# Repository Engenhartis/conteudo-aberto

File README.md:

# conteudo-aberto
Conteúdo aberto disponibilizado pela Engenhartis.

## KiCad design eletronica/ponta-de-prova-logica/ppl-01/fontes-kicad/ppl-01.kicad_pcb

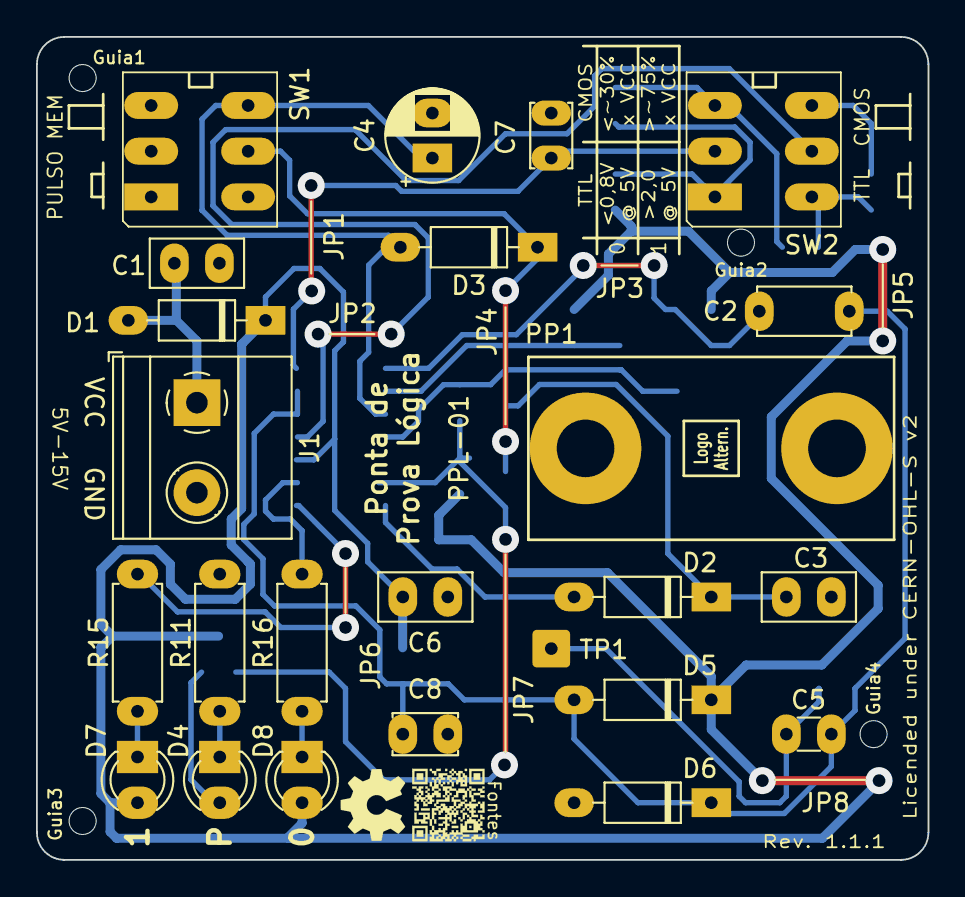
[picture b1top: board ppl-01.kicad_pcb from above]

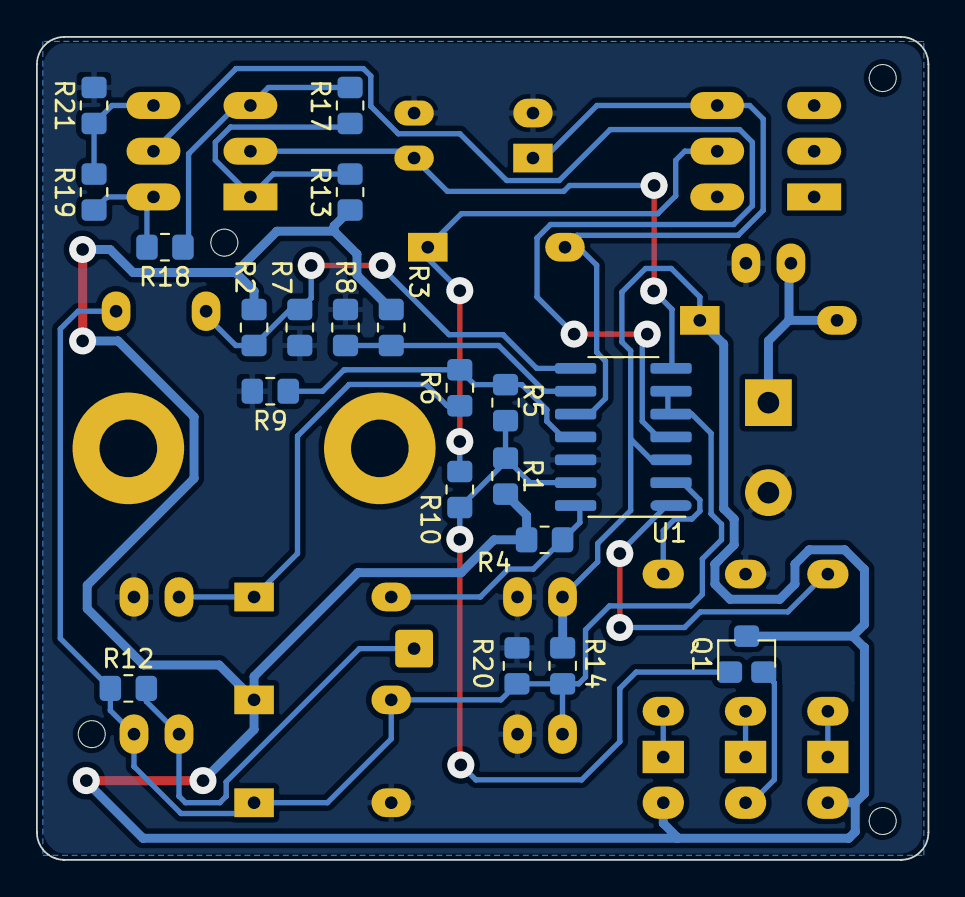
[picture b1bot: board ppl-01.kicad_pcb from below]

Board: 2 copper layers, 49.5 x 45.7 mm, 57 parts (23 on the bottom side), 25 nets.

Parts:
C1, C3, C6: 100nF; C_Disc_D5.0mm_W2.5mm_P2.50mm
C2: 1,8nF; C_Disc_D5.0mm_W2.5mm_P5.00mm
C4: 1uF/25V; CP_Radial_D5.0mm_P2.50mm
C5: 560pF; C_Disc_D3.0mm_W1.6mm_P2.50mm
C7, C8: 10nF; C_Disc_D3.4mm_W2.1mm_P2.50mm
D1, D2, D3, D5, D6: 1N4148; D_DO-35_SOD27_P7.62mm_Horizontal
D4: AM; LED_D3.0mm
D7: VD; LED_D3.0mm
D8: VM; LED_D3.0mm
Guia1, Guia2, Guia3, Guia4: FuroGuia_1.5mm
J1: Conn_01x02; TerminalBlock_Phoenix_MKDS-1,5-2_1x02_P5.00mm_Horizontal
JP1: Jumper_Simbolico; Wire_Jumper_L4.0mm
JP2, JP6: Jumper_Simbolico; Wire_Jumper_L2.5mm
JP3: Jumper_Simbolico; Wire_Jumper_L2.0mm
JP4: Jumper_Simbolico; Wire_Jumper_L6.5mm
JP5: Jumper_Simbolico; Wire_Jumper_L3.5mm
JP7: Jumper_Simbolico; Wire_Jumper_L11.0mm
JP8: Jumper_Simbolico; Wire_Jumper_L5.0mm
PP1: Ponta de Prova; Ponta_de_Prova_Fixacao_20mmx10mmx10mm
Q1: BC847; SOT-23
R1, R4, R12: 10k; R_0805_2012Metric_Pad1.20x1.40mm_HandSolder
R2: 2M7; R_0805_2012Metric_Pad1.20x1.40mm_HandSolder
R3, R8, R10: 100k; R_0805_2012Metric_Pad1.20x1.40mm_HandSolder
R5, R6, R9: 470k; R_0805_2012Metric_Pad1.20x1.40mm_HandSolder
R7: 4M7; R_0805_2012Metric_Pad1.20x1.40mm_HandSolder
R11, R15, R16: 820R/0.5W; R_Axial_DIN0207_L6.3mm_D2.5mm_P7.62mm_Horizontal
R13, R21: 47k; R_0805_2012Metric_Pad1.20x1.40mm_HandSolder
R14: 1.2M; R_0805_2012Metric_Pad1.20x1.40mm_HandSolder
R17: 82k; R_0805_2012Metric_Pad1.20x1.40mm_HandSolder
R18: 33k; R_0805_2012Metric_Pad1.20x1.40mm_HandSolder
R19: 39k; R_0805_2012Metric_Pad1.20x1.40mm_HandSolder
R20: 820k; R_0805_2012Metric_Pad1.20x1.40mm_HandSolder
R***: QR_CODE_URL_Fontes_PPL-01
SW1, SW2: SW_DPDT_x2; Button_8mm_x_8mm_H2.5mm_V5.5mm
TP1: Ponta de Prova; SolderWire-0.5sqmm_1x01_D0.9mm_OD2.1mm
U1: LM339; SOIC-14_3.9x8.7mm_P1.27mm

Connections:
GND: C1.2, C3.1, C4.2, C6.2, C7.2, C8.2, D6.2, J1.2, R7.2, R8.2, R9.2, R11.1, R20.2, R21.2, U1.12
unnamed: C1.1, D1.2, J1.1
unnamed: C2.1, R2.2, R7.1, U1.8
unnamed: C3.2, D2.1, R6.2
unnamed: C4.1, D3.2, SW1.6, U1.10
unnamed: C5.2, R12.2, TP1.1
unnamed: C7.1, SW2.2, U1.7
unnamed: D2.2, R4.2, U1.14
unnamed: D3.1, R10.2, SW1.5
unnamed: D4.1, R11.2
unnamed: D4.2, Q1.2
unnamed: D7.1, R15.1
unnamed: D8.1, R16.1
unnamed: Q1.1, R1.2, R5.1, R10.1, U1.13
unnamed: R3.2, R8.1, U1.9
unnamed: R5.2, R6.1, R9.1, U1.11
unnamed: R13.2, R17.1, SW2.1
unnamed: R15.2, U1.1
unnamed: R16.2, U1.2
unnamed: R17.2, R18.1, SW2.3
unnamed: R18.2, R19.1, SW2.4
unnamed: R19.2, R21.1, SW2.6
unnamed: SW2.5, U1.4
VCC: C6.1, D1.1, D5.1, D7.2, D8.2, Q1.3, R1.1, R2.1, R3.1, R4.1, R13.1, R14.1, U1.3
vprova: C2.2, C5.1, C8.1, D5.2, D6.1, R12.1, R14.2, R20.1, U1.5, U1.6

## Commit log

2021-07-17 Formulário de Eletromagnetismo restaurado do projeto Lalfrecom em github.com/mptrv. Criado documento filho único, com o conteúdo principal, e documentos mestres com diferentes formatações de página (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
2021-07-18 Obtenção de ícones para a licença CC-BY-SA. Adaptação de ícone de CC-BY-SA. No formulário A4: complementações de leiaute, nova redação para a apresentação, remoção das informações para obtenção do có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
2021-07-19 Conclusão da revisão final do formulário, em formato A4. Criação de 'thumbnail' para a publicação no sítio.
2021-08-04 Miniatura genérica para formulários.
2021-08-11 Formulário de Eletromagnetismo A5 em brochura (livreto).
2022-07-02 Preparação dos arquivos da ponta de prova lógica para publicação.
2022-07-04 Projeto Ponta de Prova Lógica - Modelo PPL-01 preparado conforme orientações do guia da licença CERN-OHL-S v2 e pronto para liberação.

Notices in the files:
eletronica/ponta-de-prova-logica/ppl-01/fontes-kicad/ppl-01.kicad_pcb:
Copyright 2022 Engenhartis (www.engenhartis.com.br)
Licença: CERN-OHL-S (https://ohwr.org/cern_ohl_s_v2.pdf)
Licended under CERN-OHL-S v2
